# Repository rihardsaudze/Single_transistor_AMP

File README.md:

# Single_transistor_AMP

Homework No.3  

  -Added PCB layout (16.04.2020)  
  -Generated Gerber and drill files (29.04.2020)  
  -Added BOM, SVG files for every PCB layer (09.05.2020)

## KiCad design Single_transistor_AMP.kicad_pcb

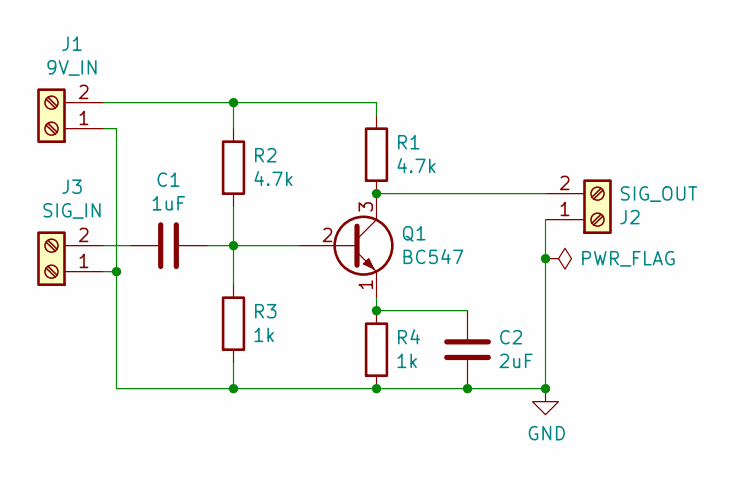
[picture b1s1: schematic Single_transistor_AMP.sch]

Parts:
C1: 1uF; C_Disc_D4.3mm_W1.9mm_P5.00mm
C2: 2uF; C_Disc_D4.7mm_W2.5mm_P5.00mm
J1: 9V_IN; TerminalBlock_bornier-2_P5.08mm
J2: SIG_OUT; TerminalBlock_bornier-2_P5.08mm
J3: SIG_IN; TerminalBlock_bornier-2_P5.08mm
Q1: BC547; TO-92_Inline
R1, R2: 4.7k; R_Axial_DIN0207_L6.3mm_D2.5mm_P10.16mm_Horizontal
R3, R4: 1k; R_Axial_DIN0207_L6.3mm_D2.5mm_P10.16mm_Horizontal

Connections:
GND: C2.1, J1.1, J2.1, J3.1, R3.2, R4.2
unnamed: C1.1, Q1.2 (B), R2.2, R3.1
unnamed: C1.2, J3.2
unnamed: C2.2, Q1.1 (E), R4.1
unnamed: J1.2, R1.1, R2.1
unnamed: J2.2, Q1.3 (C), R1.2

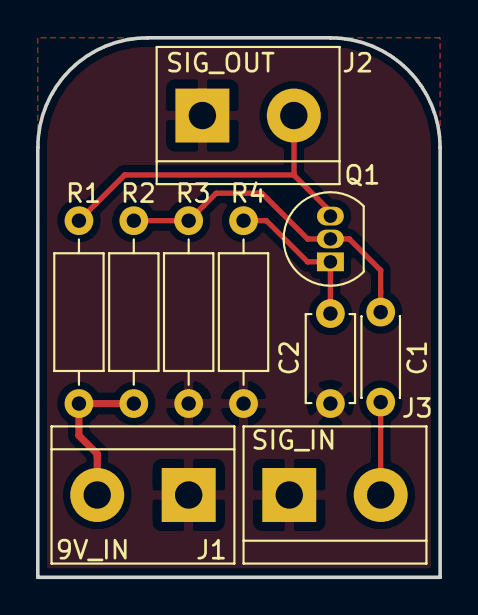
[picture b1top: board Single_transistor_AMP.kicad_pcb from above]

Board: 2 copper layers, 22.4 x 30.0 mm, 10 parts (0 on the bottom side), 6 nets.

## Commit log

2020-03-18 Initial commit, basic schematic done
2020-03-18 Added footprints, annotations, datasheets and generated netlist file
2020-04-01 Disabled unnecessary layers, added design rules
2020-04-16 Set design rules, created PCB layout and traces, positioned labels
2020-04-24 Fixed a DRC issue, improved traces
2020-04-29 Added GERBER and DRILL files
2020-05-09 Added BOM, SVG files for every PCB layer
2020-05-13 Fixed BOM formatting
